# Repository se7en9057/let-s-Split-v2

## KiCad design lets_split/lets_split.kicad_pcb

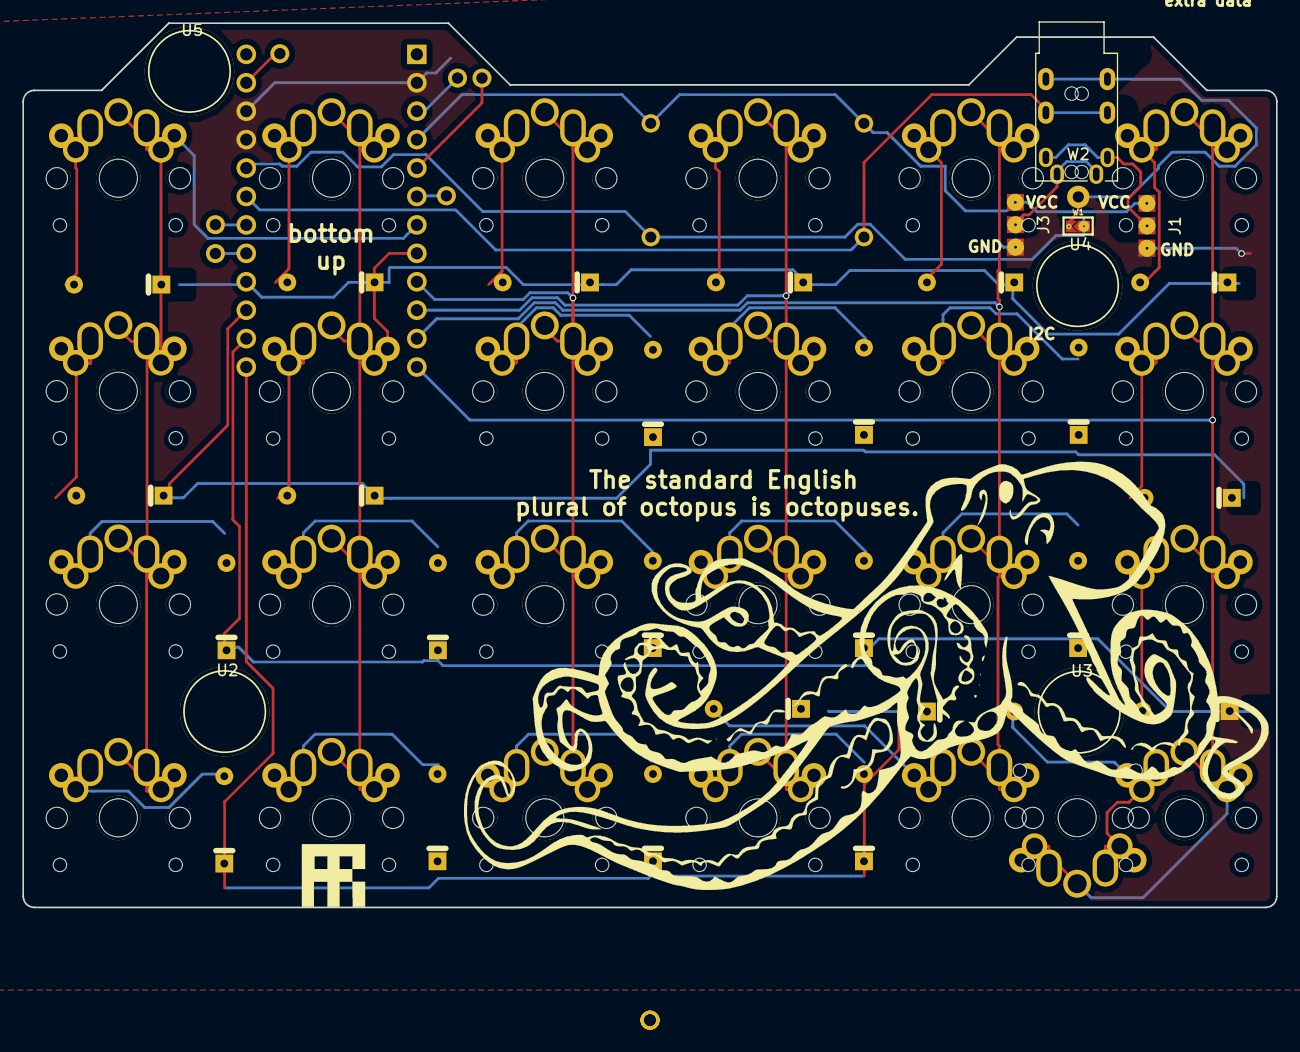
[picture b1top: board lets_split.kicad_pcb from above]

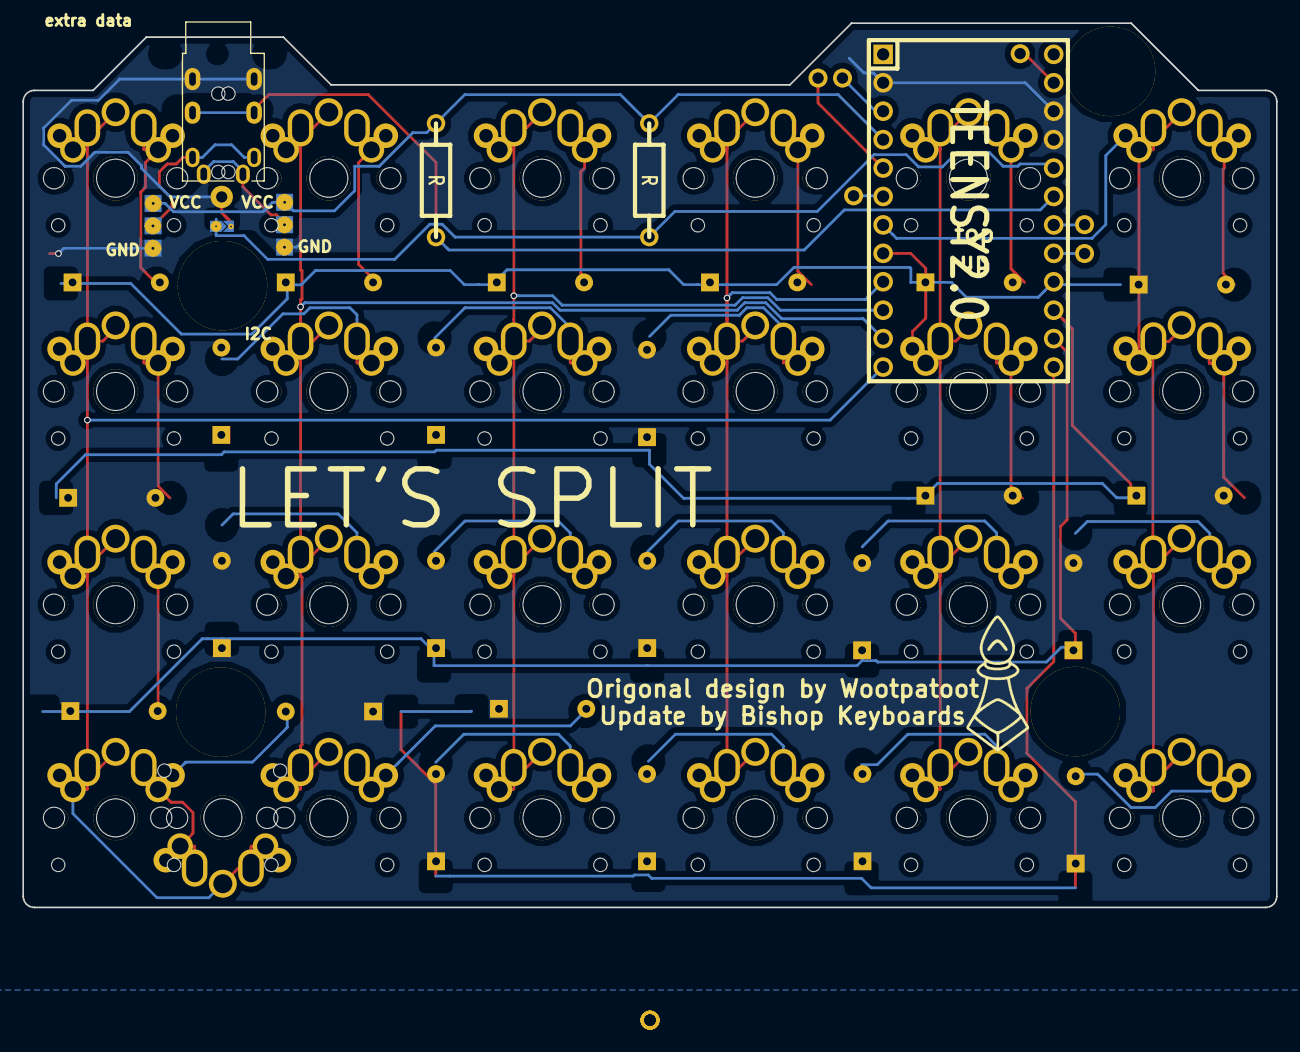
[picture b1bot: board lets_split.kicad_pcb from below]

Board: 2 copper layers, 112.0 x 79.0 mm, 70 parts (3 on the bottom side), 47 nets.

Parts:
D1, D2, D3, D4, D5, D6, D7, D8, D9, D10, D11, D12, D13, D14, D15, D16, D17, D18, D19, D20, D21, D22, D23, D24: D; D_axial_clean
J1, J3: 3PIN; jumper
J4, J5, J6, J7, J8, J9, J10, J11, J12: Conn_01x01; PIN_1
R1, R2: R; RESISTOR
SW1, SW2, SW3, SW4, SW5, SW6, SW7, SW8, SW9, SW10, SW11, SW12, SW13, SW14, SW15, SW16, SW17, SW18, SW19, SW20, SW21, SW22, SW23, SW24, SW25: SW_PUSH; MX-ALPs-PG1350-FLIP
TRRS1: 4pin 3.5mm; PJ320E_3.5mm_Jack_flip
U1: TEENSY2.0; TEENSY_2.0
U2, U3, U4, U5: HOLE
W1: TEST; JUMPER_SMD_2DUB
W2: TEST_1P; SolderWirePad_single_2mmDrill

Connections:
GND: J1.1, J3.1, U1.2, U1.26, U1.27
unnamed: D1.2, SW1.2
unnamed: D2.2, SW2.2
unnamed: D3.2, SW3.2
unnamed: D4.2, SW4.2
unnamed: D5.2, SW5.2
unnamed: D6.2, SW6.2
unnamed: D7.2, SW7.2
unnamed: D8.2, SW8.2
unnamed: D9.2, SW9.2
unnamed: D10.2, SW10.2
unnamed: D11.2, SW11.2
unnamed: D12.2, SW12.2
unnamed: D13.2, SW13.2
unnamed: D14.2, SW14.2
unnamed: D15.2, SW15.2
unnamed: D16.2, SW16.2
unnamed: D17.2, SW17.2
unnamed: D18.2, SW18.2
unnamed: D19.2, SW19.2
unnamed: D20.2, SW20.2
unnamed: D21.2, SW21.2
unnamed: D22.2, SW22.2
unnamed: D23.2, SW23.2
unnamed: D24.2, SW24.2, SW25.2
unnamed: J1.2, TRRS1.1
unnamed: J3.2, TRRS1.4
unnamed: J4.1, U1.3
unnamed: J5.1, U1.5
unnamed: J6.1, U1.22
unnamed: J7.1, U1.6
unnamed: J11.1, U1.28
unnamed: J12.1, U1.23
unnamed: R1.2, U1.25, W1.2
VCC: J1.3, J3.3, R1.1, R2.2, U1.4
col0: SW1.1, SW2.1, SW3.1, SW4.1, U1.7
col1: SW5.1, SW6.1, SW7.1, SW8.1, U1.8
col2: SW9.1, SW10.1, SW11.1, SW12.1, U1.9
col3: SW13.1, SW14.1, SW15.1, SW16.1, U1.10
col4: SW17.1, SW18.1, SW19.1, SW20.1, U1.11
col5: SW21.1, SW22.1, SW23.1, SW24.1, SW25.1, U1.12
data: R2.1, TRRS1.2, U1.24
row0: D1.1, D5.1, D9.1, D13.1, D17.1, D21.1, U1.21
row1: D2.1, D6.1, D10.1, D14.1, D18.1, D22.1, U1.20
row2: D3.1, D7.1, D11.1, D15.1, D19.1, D23.1, U1.19
row3: D4.1, D8.1, D12.1, D16.1, D20.1, D24.1, U1.18
xtradata: TRRS1.3, W1.1, W2.1

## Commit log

2018-05-31 added universal switch and stuff
2018-05-31 fixed diodes broke traces
    updated the diode footprint will have to fix traces now that the width of the diode pole spaces are different.
2018-06-02 changed 3.5mm jack
    updated 3.5mm jack to use the PJ320E
